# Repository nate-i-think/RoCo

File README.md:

# RoCo

This is a rowing (and later industrial surveying) telemetry computer and 5mm precision GPS that I designed for my first company, Precision Metrics. I taught myself hardware and made this as my first ever project in July of 2025, approximately. It worked first try, with one minor solder job :)

This repository is a monolith assembled by Claude to demonstrate my work. Most everything here besides its present organization was created by hand. This was my first engineering project; you can see the improvement between the daughterboard (my first PCB) and the mainboard (my second). 

For the boards, I used KiCad; for the enclosure, FreeCAD; and for the firmware, nothing but Rust, cross-compiled for the Pi. I recommend looking at the schematics and layout of the PCB.

A thank you to Phil's Lab and all the lovely YouTube tutorials which RL'd my brain.

All text and images henceforth are written and compiled by Claude to demonstrate the technical work I did.

RoCo is a rowing telemetry computer. It is built around a Raspberry Pi Compute Module 4 with a u-blox ZED-F9P RTK GNSS receiver (L1/L5), a Quectel BG95 LTE-M modem, a 5-inch 800×480 display, an IMU and magnetometer, haptic feedback, and a Li-ion battery that charges over USB-C or Qi. The dashboard mockups show split per 500 m, stroke rate, distance per stroke, check, and session totals. I designed it in 2025–26 at Precision Metrics, my hardware startup.

This repository holds the four KiCad boards, the FreeCAD enclosure, and the Rust firmware that runs on the CM4. The boards carry the internal name RowCore: MB1 is the mainboard, DB1 the power board.

## System

```mermaid
flowchart LR
    subgraph DB1["Power board (DB1)"]
        usbc["USB-C"]
        qi["Qi receiver<br/>BQ51013B"]
        orr["Input OR<br/>TPS2117"]
        chg["Charger<br/>MAX77757"]
        bat["Li-ion cell<br/>BQ27441 gauge"]
        boost["5 V buck-boost<br/>RT6154"]
        usbmux["USB mux<br/>PI3USB102"]
        gpx["GPIO expander<br/>PCAL6524"]
    end

    keys["Button panel<br/>6 switches"]

    subgraph MB1["Mainboard (MB1)"]
        cm4["Raspberry Pi<br/>CM4 Lite"]
        gnss["ZED-F9P<br/>RTK GNSS"]
        lte["BG95-M2<br/>LTE-M"]
        tfp["TFP401<br/>HDMI to RGB"]
        rails["Panel supplies<br/>+10 V, +18 V, -10 V, LED"]
        imu["IMU + magnetometer<br/>LSM6DSOX, IIS2MDC"]
        hap["Haptics<br/>DRV2605L + LRA"]
        sd["microSD"]
    end

    lcd["5 in 800x480<br/>RGB panel"]

    usbc --> orr
    qi --> orr
    orr --> chg
    chg <--> bat
    chg --> boost
    boost -- "5 V, mezzanine" --> cm4
    usbc <--> usbmux
    usbmux -- "USB 2.0" --> cm4
    keys -- "cable" --> gpx
    gpx -- "I2C" --> cm4
    cm4 -- "HDMI" --> tfp
    tfp -- "24-bit RGB" --> lcd
    rails --> lcd
    cm4 -- "UART" --> gnss
    cm4 -- "UART" --> lte
    cm4 -- "I2C" --> imu
    cm4 -- "I2C" --> hap
    cm4 -- "SDIO" --> sd
```

The mainboard and power board stack on a 20-pin Samtec LSHM mezzanine that carries 5 V, 3.3 V, USB, I²C, I²S, and interrupt lines. The button panel is wired to the power board's switch inputs, with Molex Pico-Lock connectors on both boards.

## Boards

Numbers come from `kicad-cli pcb export stats` on the files in this repository.

| Board | Folder | Copper layers | Size | Footprints | Vias |
|---|---|---|---|---|---|
| Mainboard (MB1, v0.1.0) | [`hardware/mainboard`](hardware/mainboard) | 4 | 111.5 × 75.7 mm | 229 (112 top, 117 bottom) | 1,013 |
| Power board (DB1, v0.2.0) | [`hardware/power-board`](hardware/power-board) | 4 | 66.0 × 42.35 mm | 109 (all top) | 290 |
| Button panel (v0.1.0) | [`hardware/button-panel`](hardware/button-panel) | 2 | 55.0 × 17.0 mm | 17 (13 top, 4 bottom) | 6 |
| U.FL adapter | [`hardware/ufl-adapter`](hardware/ufl-adapter) | 2 | 10.0 × 13.5 mm | 2 | 12 |

- **Mainboard.** CM4 Lite carrier on two Hirose DF40 board-to-board connectors. It holds the ZED-F9P with active-antenna bias and its own low-noise LDOs, a backup cell, and a debug USB-C port. Next to it are the BG95-M2 with a nano-SIM and a 1.8 V to 3.3 V level shifter, and a TFP401 HDMI receiver driving the panel's RGB interface. Display power comes from an MP3308 backlight driver, two LMR62014 boosts (+10 V AVDD, +18 V VGH) and an ICL7660 charge pump (−10 V VGL). The board also carries 3.3 V and 3.6 V bucks, microSD, the LSM6DSOX IMU, the IIS2MDC magnetometer, and a DRV2605L haptic driver.
- **Power board.** USB-C and a Qi receiver (BQ51013B) are ORed by a TPS2117 into a MAX77757 charger, with a BQ27441 fuel gauge and reverse-polarity protection on the cell. An RT6154 buck-boost makes the 5 V system rail, and an STM6601 push-button controller handles power on and off. A PI3USB102 switches the USB-C data lines between charger negotiation and the CM4. A PCAL6524 I²C expander reads the buttons and drives the enables.
- **Button panel.** Six Panasonic EVQ-Q2U03W switches on a 55 mm strip. The enclosure has a matching TPU button cover.
- **U.FL adapter.** A short grounded coplanar trace with a via fence between a TE Connectivity CONMHF1 receptacle and a Hirose U.FL.

## Design highlights

- **HDMI to RGB.** The CM4's HDMI0 output feeds a TI TFP401 DVI receiver, which drives the panel's 24-bit RGB bus through 33 Ω series-termination arrays. A 24LC02 EEPROM on the DDC lines supplies EDID and can be programmed in production through a TC2030 footprint.
- **Controlled impedance.** Five differential pairs need it: four 100 Ω HDMI TMDS pairs on L1 over the L2 plane, and the 90 Ω USB 2.0 pair on L4 over L3. Three RF feeds use 50 Ω coplanar waveguide: the ZED-F9P antenna input and the BG95's main and GNSS antennas. The trace geometry, the fab stackup and the impedance spec sent with the gerbers are [below](#stackup-and-impedance-control).
- **Length tuning.** KiCad tuning meanders even out lengths on the ZED-F9P USB pair, one HDMI TMDS lane, and parts of the RGB bus.
- **Double-sided assembly.** The mainboard has 112 footprints on top and 117 on the bottom, routed at 0.15 mm track and space with 0.2 mm drilled vias. In1 is a solid ground plane under the L1 signals, and In2 carries ground, 5 V and the display supplies.

## Gallery

### Board renders

<table>
  <tr>
    <td align="center"><br>Mainboard, top</td>
    <td align="center"><br>Mainboard, bottom</td>
  </tr>
  <tr>
    <td align="center"><br>Power board, top</td>
    <td align="center"><br>Power board, bottom</td>
  </tr>
  <tr>
    <td align="center" colspan="2"><br>Button panel, top</td>
  </tr>
</table>

The mainboard renders went to the fab with the gerbers; the power board and button panel renders show bare pads wherever a third-party 3D model is not in this repository.

### Enclosure

<p align="center">
  
</p>

Case prototype 2 ([`RoCo_case_prototype_2.FCStd`](hardware/enclosure/RoCo_case_prototype_2.FCStd)), with the parts in their model positions, display side up: the shell at the bottom, the PCB bracket, the display bracket on top, and the TPU cover for the button panel to the right. The 3MF print exports are in [`hardware/enclosure`](hardware/enclosure).

### Schematics

<table>
  <tr>
    <td align="center"><br>Mainboard: root sheet and mezzanine</td>
    <td align="center"><br>Mainboard: CM4 high-speed, TFP401, display FPC</td>
  </tr>
  <tr>
    <td align="center"><br>Mainboard: CM4 GPIO, BG95, ZED-F9P</td>
    <td align="center"><br>Mainboard: display supplies, 3V3 and 3V6 bucks</td>
  </tr>
  <tr>
    <td align="center"><br>Mainboard: microSD, IMU, magnetometer, haptics</td>
    <td align="center"><br>Power board (single sheet)</td>
  </tr>
</table>

Click a thumbnail for the full sheet (A3 at 150 dpi). The KiCad sources are [`hardware/mainboard/rowcore 0.1.0.kicad_sch`](hardware/mainboard/rowcore%200.1.0.kicad_sch) and [`hardware/power-board/rowcore 0.1.0-power-no-audio.kicad_sch`](hardware/power-board/rowcore%200.1.0-power-no-audio.kicad_sch).

### Stackup and impedance control

This is the fab's standard 1.6 mm four-layer stackup, used for the impedance calculations: 0.1785 mm of 7628 prepreg (εr 4.74) on each side of a 1.03 mm core (εr 4.6), 1 oz inner copper, and ½ oz outer copper plated to 1 oz. The fab's stackup sheet is in [`_stackup.pdf`](hardware/mainboard/Manufacturing/_stackup.pdf) (also as a [PNG](hardware/docs/images/stackup-fab.png)).

Trace geometry was set with the fab's impedance calculator against that stackup ([`Impedence Control.csv`](hardware/mainboard/Manufacturing/Impedence%20Control.csv)):

| # | Type | Signal layer | Reference layer | Trace width (mm) | Spacing (mm) | Target impedance | Use |
|---|---|---|---|---|---|---|---|
| 1 | Differential | L4 | L3 | 0.277 | 0.2917 | 90 Ω ± 10 % differential, 45 Ω ± 10 % single-ended | USB 2.0 |
| 2 | Differential | L1 | L2 | 0.272 | 0.7 | 100 Ω ± 5 % differential, 50 Ω ± 10 % single-ended | HDMI |
| 3 | Coplanar waveguide | L1 | L2 | 0.377396 | — | 50 Ω ± 10 % | RF |

The impedance spec that went out with the gerbers ([PDF](hardware/mainboard/Manufacturing/rowcore_gerbers/Impedence%20Control%20Specifics.pdf)) marks each controlled trace on the layout: the USB 2.0 pair, the four HDMI pairs and the three RF feeds.

### Mainboard copper

Each copper layer plotted with the board outline, seen from the top.

<table>
  <tr>
    <td align="center"><br>L1 · F.Cu</td>
    <td align="center"><br>L2 · In1.Cu (solid ground plane)</td>
  </tr>
  <tr>
    <td align="center"><br>L3 · In2.Cu (ground, 5 V and display supplies)</td>
    <td align="center"><br>L4 · B.Cu</td>
  </tr>
</table>

## Firmware

[`firmware/`](firmware) is a single Rust crate (edition 2024, about 6,700 lines) for Raspberry Pi OS on the CM4. It runs on a single-threaded Tokio runtime, since the work is I/O-bound.

| Module | Lines | What it does |
|---|---|---|
| [`src/io/ubx.rs`](firmware/src/io/ubx.rs) | 2,706 | UBX protocol: framing, Fletcher-8 checksums, and typed decoders for NAV-PVT, NAV-HPPOSLLH, NAV-RELPOSNED, NAV-SIG, NAV-SAT, NAV-DOP, NAV-SVIN, MON-RF, SEC-SIG, RXM-RTCM and ACK, plus CFG-VALGET/VALSET request builders and a VALGET decoder. `UBXHub` is the async hub: one task owns the serial read half, parses frames and publishes each (class, id) on its own `watch` channel, and a second task owns the write half. `request()` registers a waiter, tagged with a per-route sequence number, before sending, so a reply that arrives immediately is not lost. |
| [`src/io/gps.rs`](firmware/src/io/gps.rs) | 477 | Opens `/dev/serial0` at the receiver's default 38,400 baud and moves UART1 to 230,400 with CFG-VALSET. It then starts the hub, a poll scheduler with a separate interval per message, and an aggregator that publishes a `GNSSFix` snapshot once a second. |
| [`src/io/debug_gnss.rs`](firmware/src/io/debug_gnss.rs) | 184 | RF health summary: C/N0 statistics, AGC level and the CW jamming indicator. |
| [`src/graphics/display.rs`](firmware/src/graphics/display.rs) | 365 | DRM/KMS renderer. It picks a connected connector (HDMI first, since the panel sits behind the TFP401), maps two XRGB8888 dumb buffers, and page-flips on vblank. The flip event is awaited through `AsyncFd`, so rendering never blocks the runtime. |
| [`src/graphics/text.rs`](firmware/src/graphics/text.rs) | 845 | Glyph atlas: rasterizes a TTF embedded at compile time with `ab_glyph` and caches the atlas on disk, validated by FNV-1a hashes of the font and charset. Glyphs are alpha-blended straight into the framebuffer, with multi-color spans. |
| [`src/graphics/debug_terminal.rs`](firmware/src/graphics/debug_terminal.rs) | 254 | `tracing` to framebuffer console. A `tracing_subscriber` layer forwards every event to an on-screen terminal, colored by level and by target, alongside the normal stdout formatter. |
| [`src/io/at.rs`](firmware/src/io/at.rs), [`src/io/cell.rs`](firmware/src/io/cell.rs) | 771 + 634 | BG95 AT driver: command and response types, a URC parser, and an `ATHub` that runs commands one at a time through a single reader/writer task, returning each response on a oneshot channel, plus a status poller for SIM, registration and signal quality. Untested on hardware, and `main.rs` does not start it yet. The parsers have unit tests. |
| [`src/main.rs`](firmware/src/main.rs) | 102 | Brings up the display and the GNSS pipeline, then renders the debug terminal with live NAV-PVT and RF-health logs. |

The UI mockup below is a full 800×480 frame, shown rotated to the panel's portrait mounting. The first firmware commit blitted these frames to the panel to preview the dashboard; the Rust code does not draw that dashboard yet.

More frames: [`fudge2.png`](firmware/docs/images/fudge2.png) (split field blanked), [`fudge3.png`](firmware/docs/images/fudge3.png), [`fudge4.png`](firmware/docs/images/fudge4.png).

### Build and deploy

The [`justfile`](firmware/justfile) cross-compiles for `aarch64-unknown-linux-gnu` and deploys over SSH. Development was on Windows, so each recipe runs cargo inside WSL.

```sh
cd firmware
just check           # cargo check
just build           # cargo build --target aarch64-unknown-linux-gnu
just build-release   # release build
just deploy          # build, scp the binary and data/ to the CM4, chmod +x, open ssh
```

Without WSL, run cargo directly, e.g. `cargo build --release --target aarch64-unknown-linux-gnu`, with an aarch64 cross linker installed. `deploy` also copies a local `data/` directory, which is not in the repository, so run `mkdir data` before the first deploy (the firmware builds its glyph cache in `data/glyphs` on the CM4).

Linking uses `aarch64-linux-gnu-gcc` (see [`.cargo/config.toml`](firmware/.cargo/config.toml)). The target host and path are variables at the top of the justfile. [`roco_boot_mods.txt`](firmware/roco_boot_mods.txt) lists the Raspberry Pi OS changes: a forced 800×480 HDMI mode for the TFP401, power-on defaults for the display-enable GPIOs, and a boot splash.

## Repository layout

```
hardware/
  mainboard/      MB1 KiCad project; Manufacturing/ has gerbers, drill files, stackup, impedance spec, BOM
  power-board/    DB1 KiCad project (v0.2.0); Manufacturing/ has gerbers and drill files
  button-panel/   KiCad project; _Exports/ has fab outputs
  ufl-adapter/    KiCad project; export/ has fab outputs
  libraries/      project symbols, footprints and 3D models
  enclosure/      FreeCAD case prototypes and 3MF print exports
  docs/images/    renders, schematics, stackup and copper plots used in this README
firmware/
  src/io/         UBX, GNSS and BG95 AT drivers
  src/graphics/   DRM/KMS display, glyph atlas, debug terminal
  docs/images/    UI mockups
```

The mainboard folder also keeps three earlier sheets (`io_battery_and_power`, `daughter_no_voice`, `daughter_with_voice`) that the root schematic no longer references. The boards and schematics embed their own copies of every symbol and footprint. A few vendor-licensed library parts are left out of `hardware/libraries/`. The files are in KiCad 9 format.

## Timeline

| When | What |
|---|---|
| Jul–Sep 2025 | Schematics and layout for the mainboard and power board |
| Sep 2025 | Gerbers for both boards, plus the mainboard stackup and impedance spec, sent to PCBWay |
| Nov 2025 | Power board v0.2.0 |
| Dec 2025–Jan 2026 | FreeCAD enclosure prototypes |
| Jan 2026 | Button panel, U.FL adapter, Rust firmware |

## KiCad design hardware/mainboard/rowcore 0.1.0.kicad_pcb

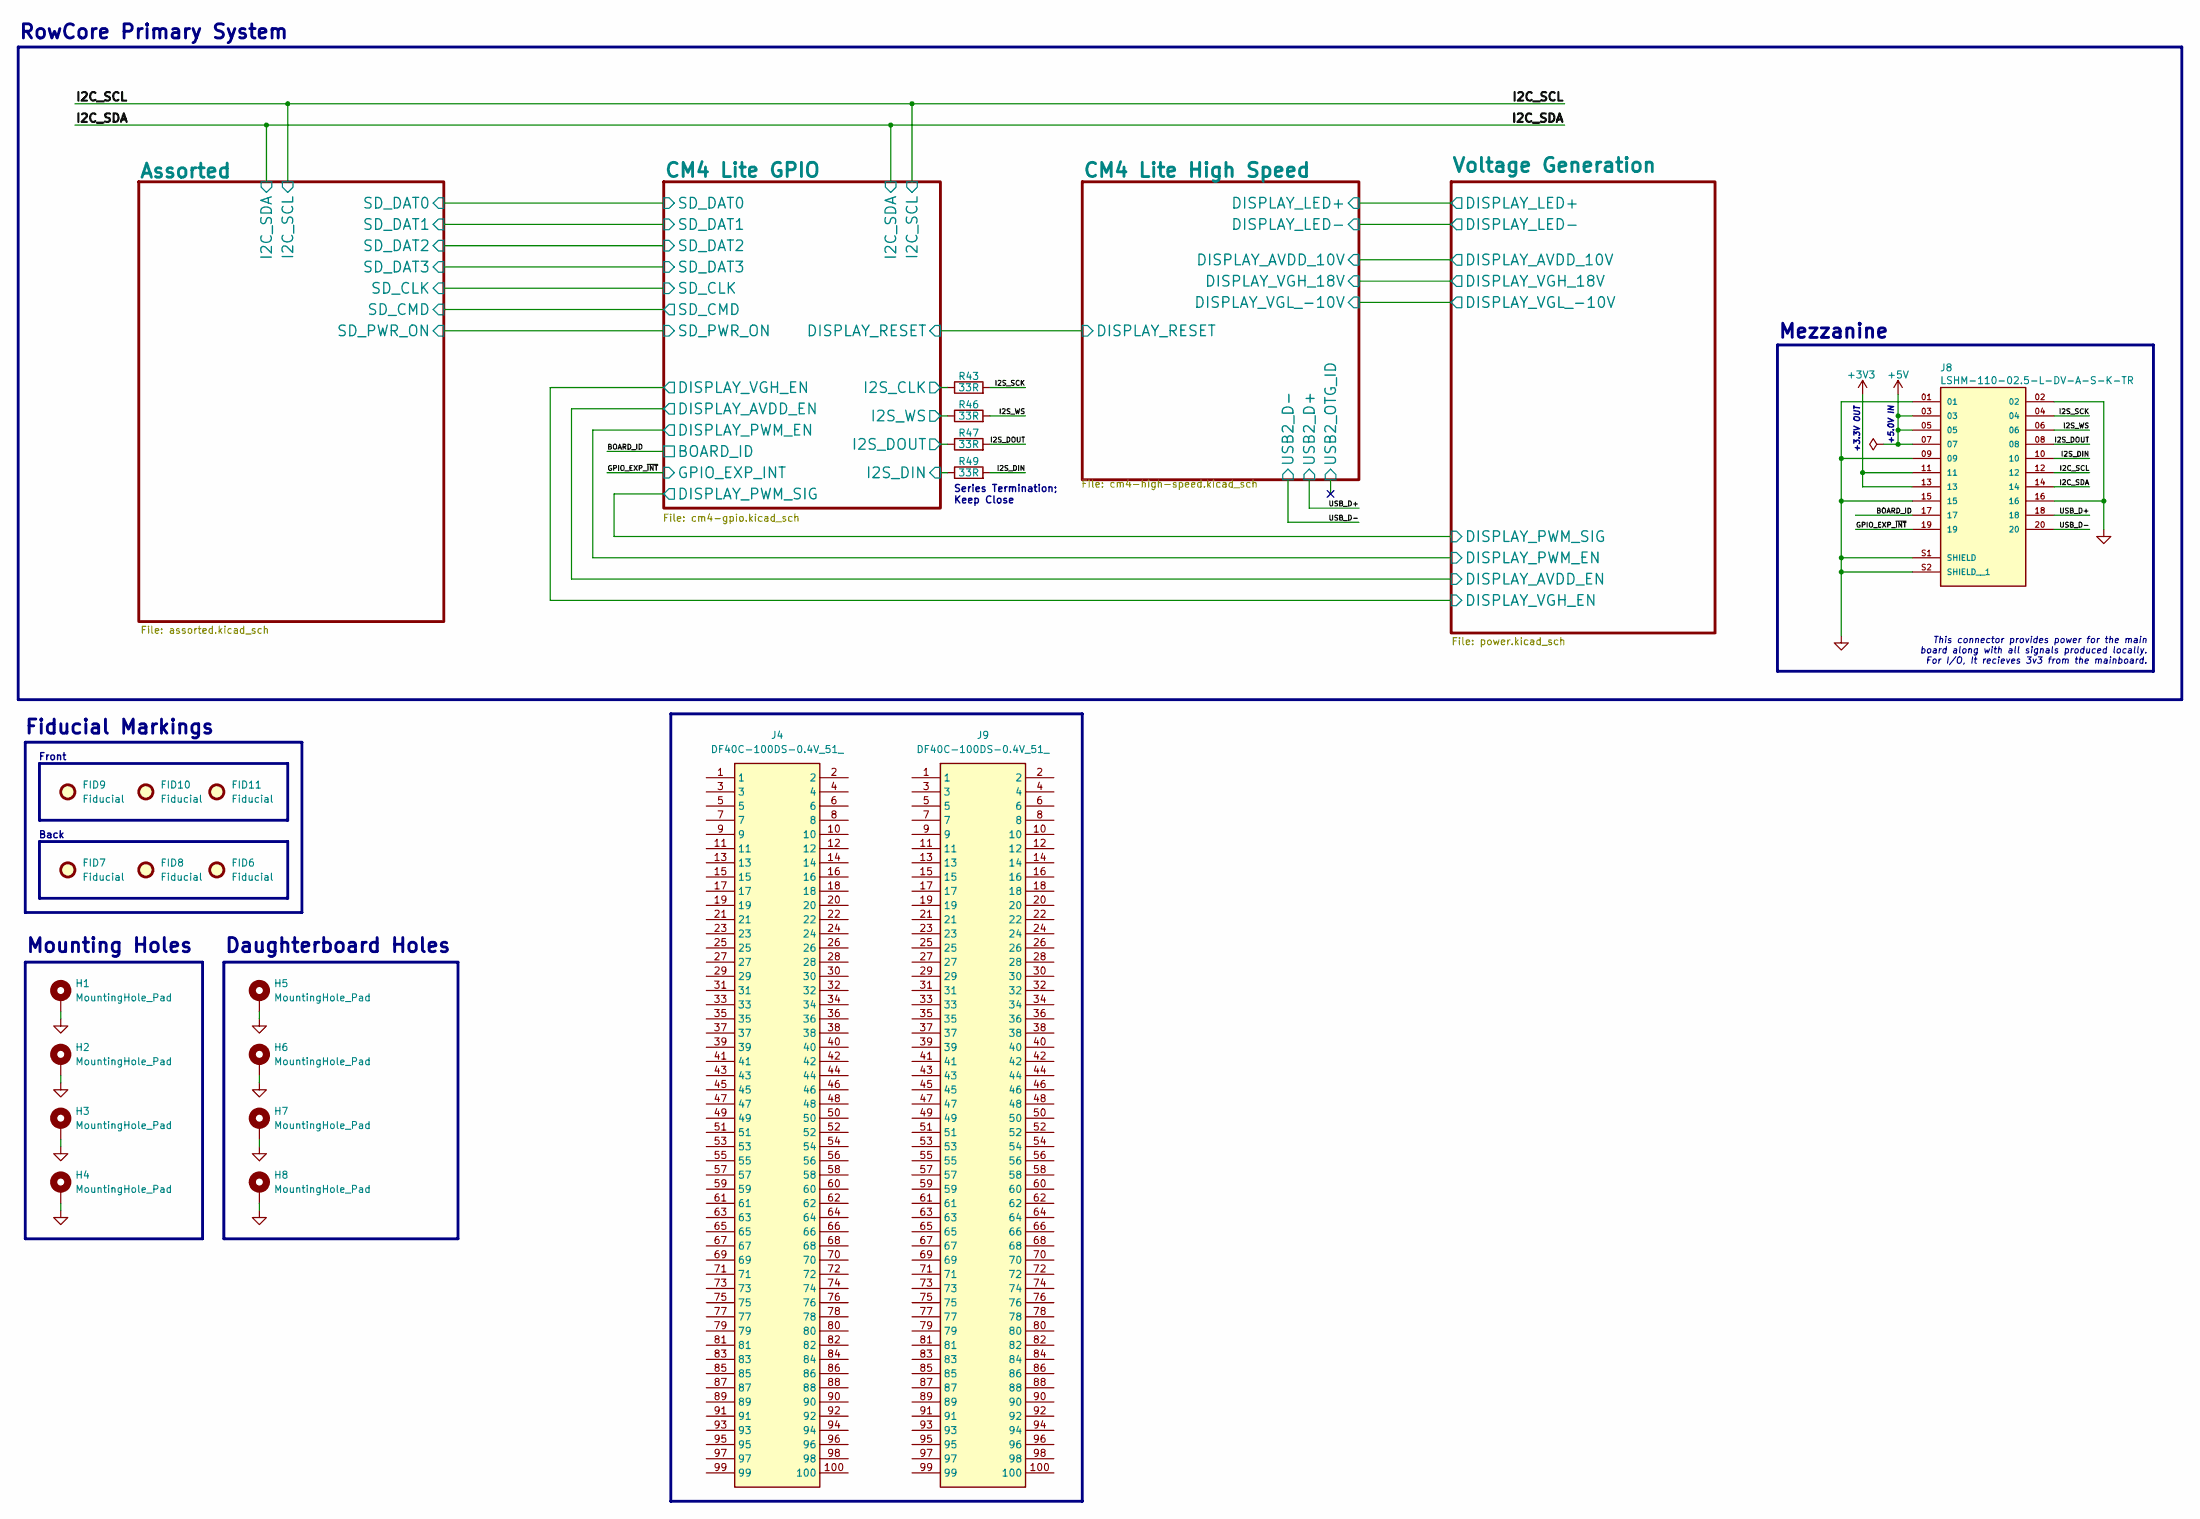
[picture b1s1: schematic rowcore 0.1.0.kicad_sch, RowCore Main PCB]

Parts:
FID6, FID7, FID8, FID9, FID10, FID11: Fiducial; Fiducial_1.5mm_Mask3mm
H1, H2, H3, H4, H5, H6, H7, H8: MountingHole_Pad; MountingHole_3mm_Pad
J4, J9: DF40C-100DS-0.4V_51_; DF40C100DS04V51; Mouser Part Number 798-DF40C100DS0.4V51
J8: LSHM-110-02.5-L-DV-A-S-K-TR; SAMTEC_LSHM-110-02.5-L-DV-A-S-K-TR; PARTREV G
R43, R46, R47, R49: 33R; R_0402_1005Metric

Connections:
+5V: J8.03, J8.05, J8.07; also elsewhere on the board
/BOARD_ID: J8.17; also elsewhere on the board
/CM4 Lite GPIO/I2S_CLK: R43.1; also elsewhere on the board
/CM4 Lite GPIO/I2S_DIN: R49.1; also elsewhere on the board
/CM4 Lite GPIO/I2S_DOUT: R47.1; also elsewhere on the board
/CM4 Lite GPIO/I2S_WS: R46.1; also elsewhere on the board
/GPIO_EXP_~INT: J8.19; also elsewhere on the board
/I2C_SCL: J8.12; also elsewhere on the board
/I2C_SDA: J8.14; also elsewhere on the board
/I2S_DIN: J8.10, R49.2
/I2S_DOUT: J8.08, R47.2
/I2S_SCK: J8.04, R43.2
/I2S_WS: J8.06, R46.2
/USB_D+: J8.18; also elsewhere on the board
/USB_D-: J8.20; also elsewhere on the board

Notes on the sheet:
Fiducial Markings
Front
Mezzanine
Mounting Holes
Series Termination; Keep Close
Back
+3.3V OUT
RowCore Primary System
Daughterboard Holes
+5.0V IN
This connector provides power for the main board along with all signals produced locally. For I/O, It recieves 3v3 from the mainboard.

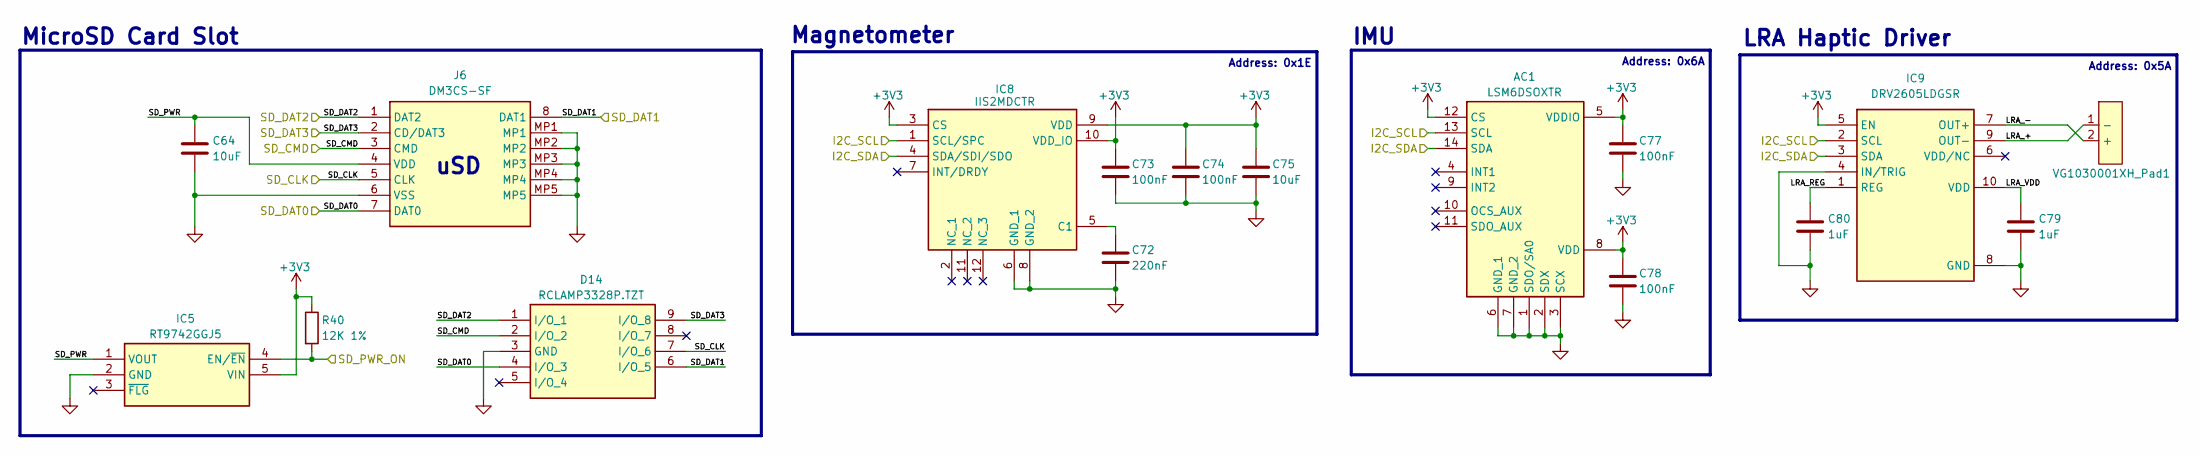
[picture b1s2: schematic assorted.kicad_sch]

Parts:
AC1: LSM6DSOXTR; LGA-14_1; Mouser Part Number 511-LSM6DSOXTR
C64, C75: 10uF; C_0805_2012Metric
C72: 220nF; C_0402_1005Metric
C73, C74, C77, C78: 100nF; C_0402_1005Metric
C79, C80: 1uF; C_0805_2012Metric
D14: RCLAMP3328P.TZT; RCLAMP3328PTZT; Mouser Part Number 947-RCLAMP3328P.TZT
IC5: RT9742GGJ5; SOT94P280X100-5N; Mouser Part Number 835-RT9742GGJ5
IC8: IIS2MDCTR; Mouser Part Number 511-IIS2MDCTR
IC9: DRV2605LDGSR; SOP50P490X110-10N; Mouser Part Number 595-DRV2605LDGSR
J6: DM3CS-SF; DM3CSSF; Mouser Part Number 798-DM3CSSF
R40: 12K 1%; R_0402_1005Metric
VG1030001XH_Pad1: VG1030001XH_Pad

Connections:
/Assorted/LRA_+: IC9.9 (OUT-), VG1030001XH_Pad1.1 (-)
/Assorted/LRA_-: IC9.7 (OUT+), VG1030001XH_Pad1.2 (+)
/Assorted/LRA_REG: C80.1, IC9.1 (REG)
/Assorted/LRA_VDD: C79.1, IC9.10 (VDD)
/Assorted/SD_CLK: D14.7 (I/O_6), J6.5 (CLK); also elsewhere on the board
/Assorted/SD_CMD: D14.2 (I/O_2), J6.3 (CMD); also elsewhere on the board
/Assorted/SD_DAT0: D14.4 (I/O_3), J6.7 (DAT0); also elsewhere on the board
/Assorted/SD_DAT1: D14.6 (I/O_5), J6.8 (DAT1); also elsewhere on the board
/Assorted/SD_DAT2: D14.1 (I/O_1), J6.1 (DAT2); also elsewhere on the board
/Assorted/SD_DAT3: D14.9 (I/O_8), J6.2 (CD/DAT3); also elsewhere on the board
/Assorted/SD_PWR: C64.1, IC5.1 (VOUT), J6.4 (VDD)
/Assorted/SD_PWR_ON: IC5.4 (EN/~EN), R40.2; also elsewhere on the board
/I2C_SCL: AC1.13 (SCL), IC8.1 (SCL/SPC), IC9.2 (SCL); also elsewhere on the board
/I2C_SDA: AC1.14 (SDA), IC8.4 (SDA/SDI/SDO), IC9.3 (SDA); also elsewhere on the board
unnamed: C72.1, IC8.5 (C1)

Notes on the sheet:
uSD
IMU
Address: 0x1E
MicroSD Card Slot
Address: 0x6A
Magnetometer
LRA Haptic Driver
Address: 0x5A

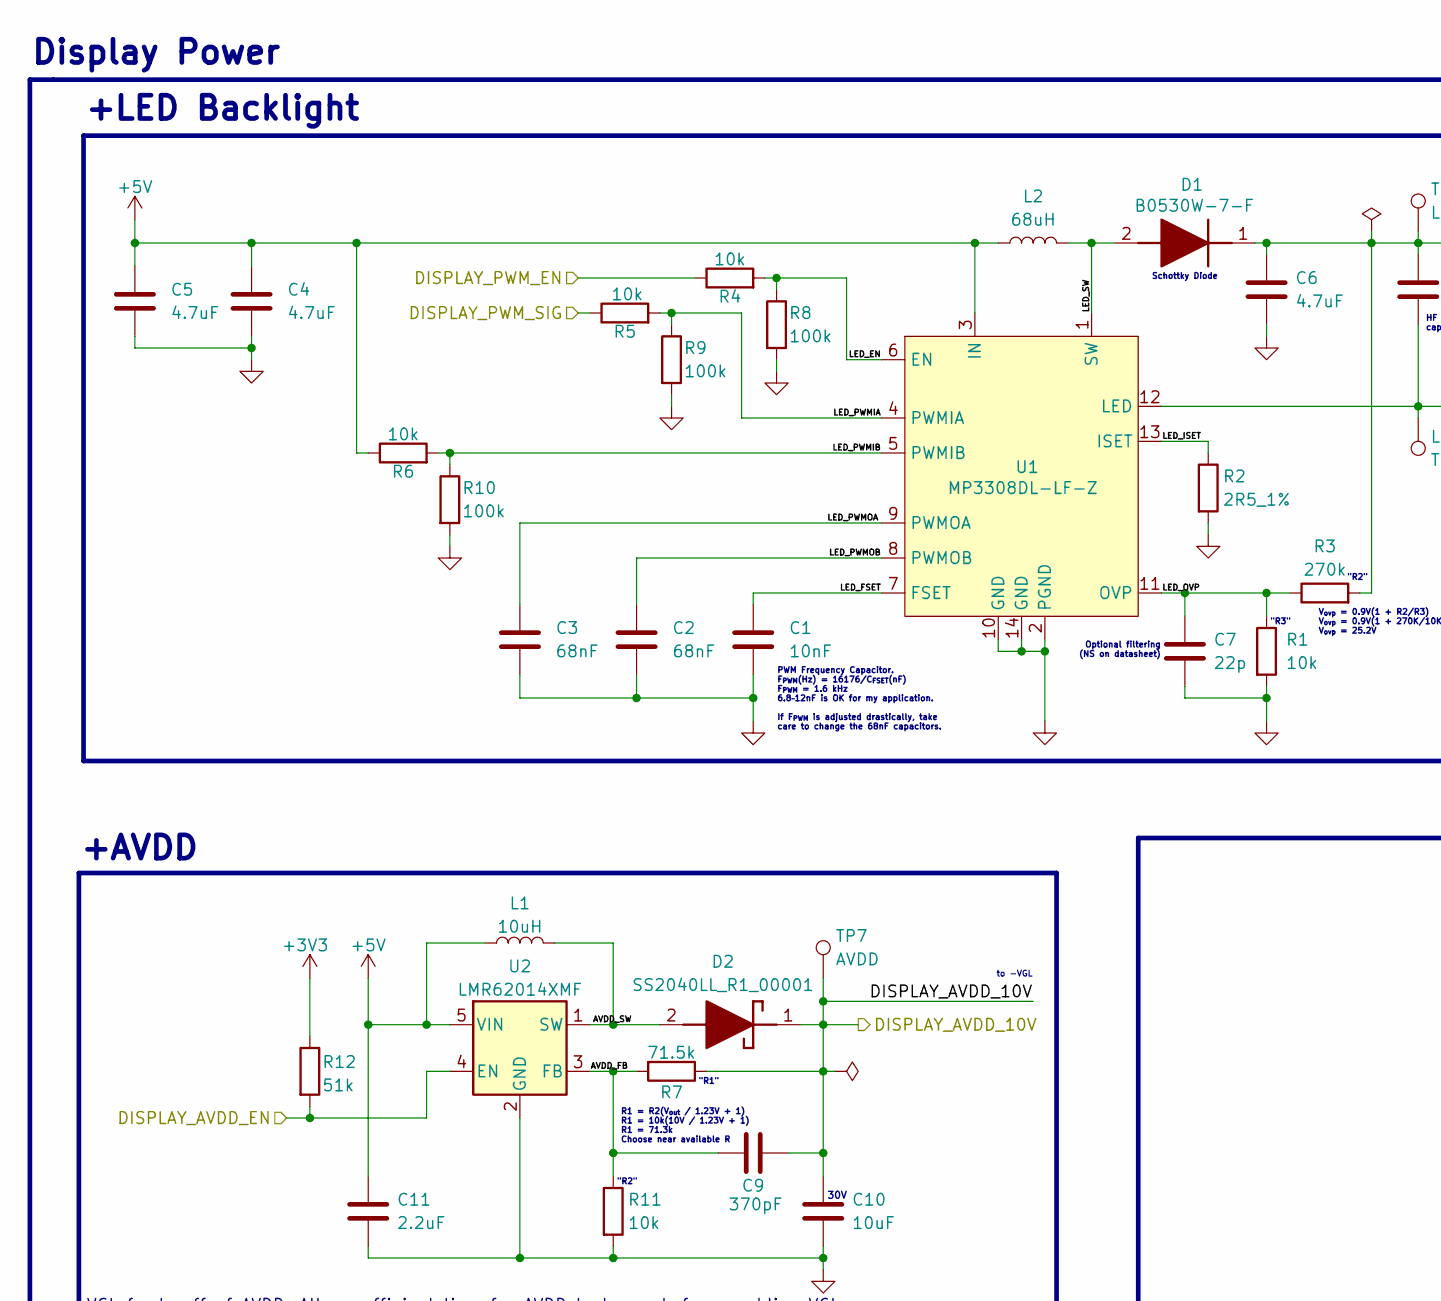
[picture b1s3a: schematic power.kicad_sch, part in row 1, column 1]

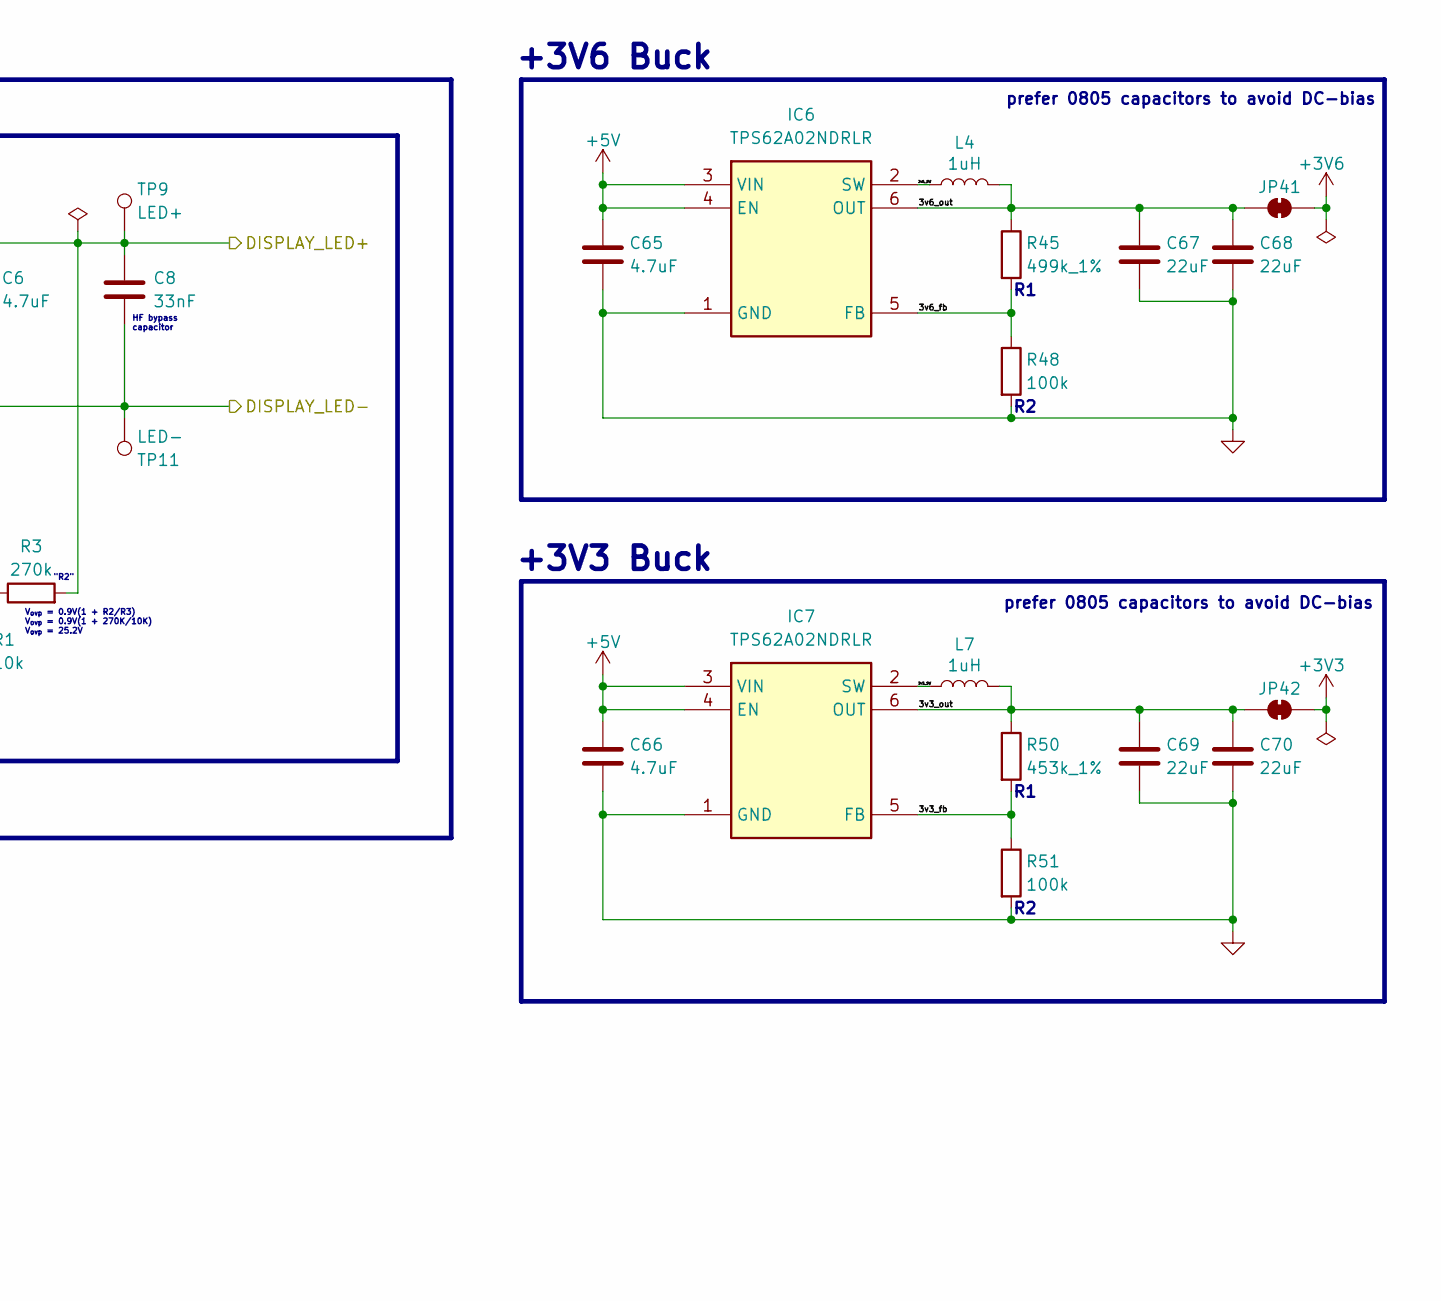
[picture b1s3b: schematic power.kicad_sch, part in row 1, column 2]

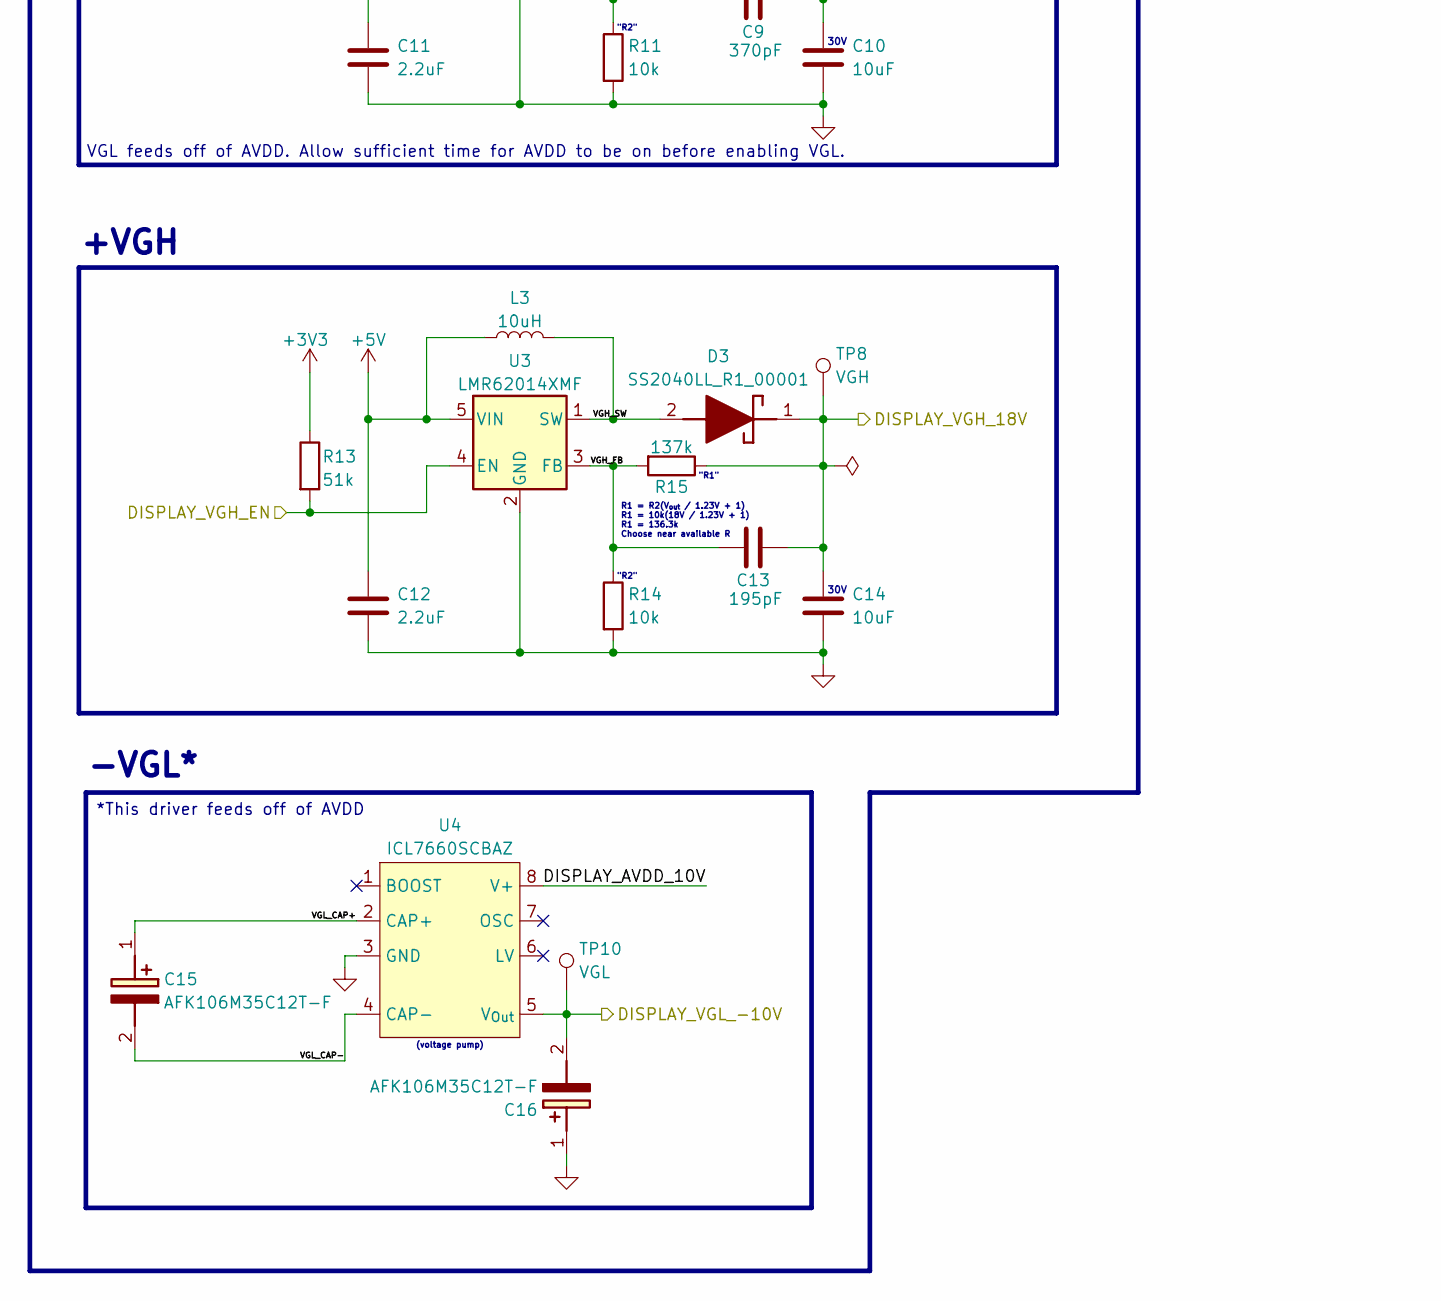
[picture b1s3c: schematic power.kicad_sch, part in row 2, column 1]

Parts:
C1: 10nF; C_0402_1005Metric
C2, C3: 68nF; C_0402_1005Metric
C4, C5, C6, C65, C66: 4.7uF; C_0805_2012Metric
C7: 22p; C_0402_1005Metric
C8: 33nF; C_0402_1005Metric
C9: 370pF; C_0402_1005Metric
C10, C14: 10uF; C_0805_2012Metric
C11, C12: 2.2uF; C_0603_1608Metric
C13: 195pF; C_0402_1005Metric
C15, C16: AFK106M35C12T-F; CAPAE530X610N; Mouser Part Number 598-AFK106M35C12T-F
C67, C68, C69, C70: 22uF; C_1206_3216Metric
D1: B0530W-7-F; SOD3716X145N; Mouser Part Number 621-B0530W-F
D2, D3: SS2040LL_R1_00001; SODFL3618X110N; Mouser Part Number 241-SS2040LLR100001
IC6, IC7: TPS62A02NDRLR; SOTFL50P160X60-6N; Mouser Part Number 595-TPS62A02NDRLR
JP41, JP42: SolderJumper_2_Bridged; SolderJumper-2_P1.3mm_Bridged_RoundedPad1.0x1.5mm
L1, L3: 10uH; NRS5040T3R3NMGJV; Manufacturer Part Number NRS5030T100MMGJ
L2: 68uH; CLF6045__; Manufacturer Part Number CLF6045NIT-680M-D
L4, L7: 1uH; DFE2HCAH1R0MJ0L
R1, R4, R5, R6, R11, R14: 10k; R_0402_1005Metric
R2: 2R5_1%; R_0603_1608Metric; Manufacturer Part Number RT0603FRE072R49L
R3: 270k; R_0402_1005Metric
R7: 71.5k; R_0603_1608Metric; Manufacturer Part Number RMCF0603FT71K5
R8, R9, R10, R48, R51: 100k; R_0402_1005Metric
R12, R13: 51k; R_0402_1005Metric
R15: 137k; R_0603_1608Metric; Manufacturer Part Number ERJ-3EKF1373V
R45: 499k_1%; R_0603_1608Metric
R50: 453k_1%; R_0603_1608Metric
TP7: AVDD; TestPoint_Pad_D1.5mm
TP8: VGH; TestPoint_Pad_D1.5mm
TP9: LED+; TestPoint_Pad_D1.5mm
TP10: VGL; TestPoint_Pad_D1.5mm
TP11: LED-; TestPoint_Pad_D1.5mm
U1: MP3308DL-LF-Z; Manufacturer Part Number MP3308DL-LF-Z
U2, U3: LMR62014XMF; SOT-23-5; Manufacturer Part Number LMR62014XMFX/NOPB
U4: ICL7660SCBAZ

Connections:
+5V: C4.1, C5.1, C11.1, C12.1, C65.1, C66.1, IC6.3 (VIN), IC6.4 (EN), IC7.3 (VIN), IC7.4 (EN), L1.1, L2.1, L3.1, R6.1, U1.3 (IN), U2.5 (VIN), U3.5 (VIN); also elsewhere on the board
/CM4 Lite GPIO/DISPLAY_AVDD_EN: R12.2, U2.4 (EN); also elsewhere on the board
/CM4 Lite GPIO/DISPLAY_PWM_EN: R4.1; also elsewhere on the board
/CM4 Lite GPIO/DISPLAY_PWM_SIG: R5.1; also elsewhere on the board
/CM4 Lite GPIO/DISPLAY_VGH_EN: R13.2, U3.4 (EN); also elsewhere on the board
/CM4 Lite High Speed/DISPLAY_LED+: C6.1, C8.1, D1.1 (K), R3.2, TP9.1; also elsewhere on the board
/CM4 Lite High Speed/DISPLAY_LED-: C8.2, TP11.1, U1.12 (LED); also elsewhere on the board
/CM4 Lite High Speed/DISPLAY_VGH_18V: C13.2, C14.1, D3.1 (K), R15.1, TP8.1; also elsewhere on the board
/CM4 Lite High Speed/DISPLAY_VGL_-10V: C16.2 (-), TP10.1, U4.5 (V_{Out}); also elsewhere on the board
/Voltage Generation/3v3_SW: IC7.2 (SW), L7.1
/Voltage Generation/3v3_fb: IC7.5 (FB), R50.2, R51.1
/Voltage Generation/3v3_out: C69.1, C70.1, IC7.6 (OUT), JP42.1 (A), L7.2, R50.1; also elsewhere on the board
/Voltage Generation/3v6_SW: IC6.2 (SW), L4.1
/Voltage Generation/3v6_fb: IC6.5 (FB), R45.2, R48.1
/Voltage Generation/3v6_out: C67.1, C68.1, IC6.6 (OUT), JP41.1 (A), L4.2, R45.1; also elsewhere on the board
/Voltage Generation/AVDD_FB: C9.1, R7.2, R11.1, U2.3 (FB)
/Voltage Generation/AVDD_SW: D2.2 (A), L1.2, U2.1 (SW)
/Voltage Generation/DISPLAY_AVDD_10V: C9.2, C10.1, D2.1 (K), R7.1, TP7.1, U4.8 (V+); also elsewhere on the board
/Voltage Generation/LED_EN: R4.2, R8.1, U1.6 (EN)
/Voltage Generation/LED_FSET: C1.1, U1.7 (FSET)
/Voltage Generation/LED_ISET: R2.1, U1.13 (ISET)
/Voltage Generation/LED_OVP: C7.1, R1.1, R3.1, U1.11 (OVP)
/Voltage Generation/LED_PWMIA: R5.2, R9.1, U1.4 (PWMIA)
/Voltage Generation/LED_PWMIB: R6.2, R10.1, U1.5 (PWMIB)
/Voltage Generation/LED_PWMOA: C3.1, U1.9 (PWMOA)
/Voltage Generation/LED_PWMOB: C2.1, U1.8 (PWMOB)
/Voltage Generation/LED_SW: D1.2 (A), L2.2, U1.1 (SW)
/Voltage Generation/VGH_FB: C13.1, R14.1, R15.2, U3.3 (FB)
/Voltage Generation/VGH_SW: D3.2 (A), L3.2, U3.1 (SW)
/Voltage Generation/VGL_CAP+: C15.1 (+), U4.2 (CAP+)
/Voltage Generation/VGL_CAP-: C15.2 (-), U4.4 (CAP-)

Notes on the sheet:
*This driver feeds off of AVDD
HF bypass capacitor
+3V6 Buck
"R3"
PWM Frequency Capacitor. F_{PWM}(Hz) = 16176/C_{FSET}(nF) F_{PWM} = 1.6 kHz 6.8–12nF is OK for my application. If F_{PWM} is adjusted drastically, take care to change the 68nF capacitors.
"R2"
-VGL*
Schottky Diode
30V
to -VGL
prefer 0805 capacitors to avoid DC-bias
V_{ovp} = 0.9V(1 + R2/R3) V_{ovp} = 0.9V(1 + 270K/10K) V_{ovp} = 25.2V
(voltage pump)
"R1"
VGL feeds off of AVDD. Allow sufficient time for AVDD to be on before enabling VGL.
+AVDD
R1 = R2(V_{out} / 1.23V + 1) R1 = 10k(18V / 1.23V + 1) R1 = 136.3k Choose near available R
+VGH
Display Power
+LED Backlight
Optional filtering (NS on datasheet)
+3V3 Buck
R1 = R2(V_{out} / 1.23V + 1) R1 = 10k(10V / 1.23V + 1) R1 = 71.3k Choose near available R
